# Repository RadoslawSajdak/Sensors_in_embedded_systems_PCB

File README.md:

# Sensors_in_embedded_systems_PCB

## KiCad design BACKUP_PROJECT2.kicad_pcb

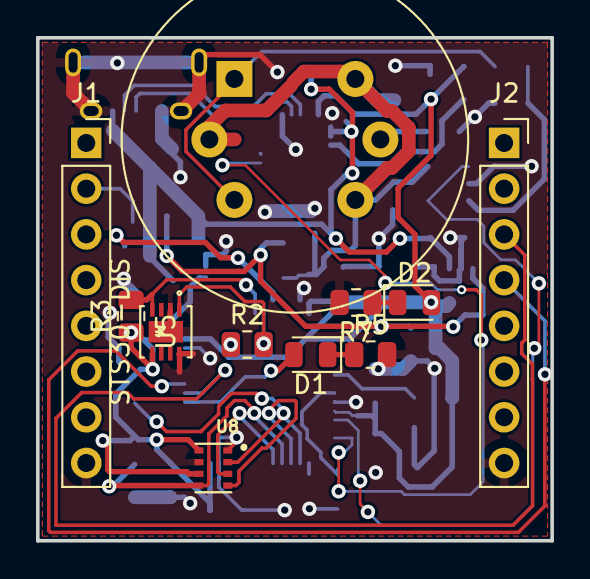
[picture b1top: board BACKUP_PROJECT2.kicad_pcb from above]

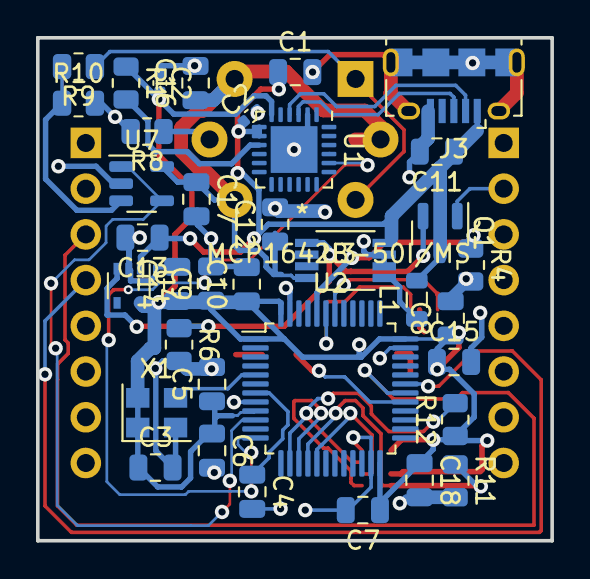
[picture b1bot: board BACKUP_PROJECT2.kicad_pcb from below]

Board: 2 copper layers, 28.6 x 27.9 mm, 47 parts (36 on the bottom side), 29 nets.

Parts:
C1, C5, C13, C14: 1u; C_0805_2012Metric
C2, C2#2: 0.1u; C_0402_1005Metric
C3: 18p; C_0805_2012Metric
C4: 0.1u; C_0805_2012Metric
C6: 10n; C_0805_2012Metric
C7, C8, C9, C15, C16, C17, C18: 100n; C_0805_2012Metric
C10: 4.7u; C_0805_2012Metric
C11, C12: 10u; C_0805_2012Metric
D1: LED_GREEN; LED_0805_2012Metric
D2: LED_RED; LED_0805_2012Metric
J1, J2: Conn_01x08_Female; PinSocket_1x08_P2.54mm_Vertical
J3: USB_B_Micro; USB_Micro-B_Amphenol_10118194_Horizontal
L1: 4.7u; L_0805_2012Metric
Q1: 2N7002; SOT-23
R1: 4.7k; R_0805_2012Metric
R2, R3, R4, R6, R8, R11, R12: 10k; R_0805_2012Metric
R5, R7: 1k; R_0805_2012Metric
R9: 2k; R_0805_2012Metric
R10: 3k; R_0805_2012Metric
U1: QFN-24-1EP_4x4mm_P0.5mm_EP2.6x2.6mm
U2: STM32F103C8Tx; LQFP-48_7x7mm_P0.5mm
U3: MCP1642B-50I/MS; MCP1642B-50I&slash_MS
U4: MIC5366-3.3YC5; SOT-353_SC-70-5
U5: STS30-DIS
U6: MQ-6
U7: LMV7219M5; SOT-23-5
U8: BMP280; XDCR_BMP280
X1: ASE-8MHz; Oscillator_SMD_Abracon_ASE-4Pin_3.2x2.5mm

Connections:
+3V3: C2#2.2, C3.1, C5.1, C6.1, C7.1, C8.1, C9.1, C10.1, C14.1, C15.1, C18.1, D2.2 (A), R1.1, R2.1, R3.1, R12.1, U1.6 (VDD), U2.1 (VBAT), U2.9 (VDDA), U2.24 (VDD), U2.36 (VDD), U2.48 (VDD), U4.5 (VOUT), U5.5 (VDD), U8.6 (VDDIO), U8.8 (VDD), X1.1 (EN), X1.4 (Vdd)
+5V: C12.1, C16.1, C17.1, U3.4 (Vout), U6.2 (VH+), U6.4 (A2), U6.6 (A1), U7.5 (V+)
/ADC1_IN0: U2.10 (PA0), U7.1, U7.4 (-)
/Power_sheet/D+: J3.3 (D+), U1.3 (D+)
/Power_sheet/D-: J3.2 (D-), U1.4 (D-)
/RST: J1.2, Q1.1 (G)
/SCL: R3.2, U2.42 (PB6), U5.4 (SCL)
/SDA: R2.2, U2.43 (PB7), U5.1 (SDA)
/SPI1_MISO: R11.1, U2.16 (PA6), U8.5 (SDO)
/SPI1_MOSI: U2.17 (PA7), U8.3 (SDI)
/SPI1_NSS: R12.2, U2.14 (PA4), U8.2 (CSB)
/SPI1_SCK: U2.15 (PA5), U8.4 (SCK)
/USART1_RX: J2.4, U2.31 (PA10)
/USART1_TX: J2.3, U2.30 (PA9)
/USART2_TX: U1.20 (RXD), U2.12 (PA2)
GND: C1.2, C2.2, C2#2.1, C3.2, C4.2, C5.2, C6.2, C7.2, C8.2, C9.2, C10.2, C11.2, C12.2, C13.2, C14.2, C15.2, C16.2, C17.2, C18.2, J1.8, J2.8, J3.5 (GND), J3.6 (Shield), R4.2, R5.2, R6.2, R7.2, R8.2, R10.2, R11.2, U1.2 (GND), U1.25 (GND), U2.8 (VSSA), U2.23 (VSS), U2.35 (VSS), U2.47 (VSS), U3.6 (Pgnd), U3.7 (Sgnd), U4.2 (GND), U5.2 (ADDR), U5.8 (VSS), U5.9 (VSS), U7.2 (V-), U8.1 (GND), U8.7 (GND), X1.2 (GND)
unnamed: C4.1, U2.7 (NRST)
unnamed: D1.1 (K), R5.1
unnamed: D1.2 (A), U2.29 (PA8)
unnamed: D2.1 (K), R7.1
unnamed: L1.1, U3.5 (SW)
unnamed: Q1.2 (S), R6.1, U3.1 (EN), U4.3 (EN)
unnamed: R1.2, U1.9 (~RST)
unnamed: R4.1, U2.44 (BOOT0)
unnamed: R8.1, U6.5 (VH-)
unnamed: R9.1, U6.1 (B1), U6.3 (B2)
unnamed: R9.2, R10.1, U7.3 (+)
unnamed: U2.5 (PD0), X1.3 (OUT)
VBUS: C1.1, C2.1, C11.1, C13.1, J3.1 (VBUS), L1.2, Q1.3 (D), U1.7 (VREGIN), U1.8 (VBUS), U3.8 (Vin), U4.1 (VIN)

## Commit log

2022-04-12 PCB design
2022-05-16 updated everything a little

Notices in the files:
parts and their libraries:
Copyright 2021 Accelerated Designs. All rights reserved.
